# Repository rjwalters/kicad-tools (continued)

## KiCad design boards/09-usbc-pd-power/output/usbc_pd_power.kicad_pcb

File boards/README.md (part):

# kicad-tools Demo Boards

PCB designs and developing examples demonstrating kicad-tools capabilities. Each board includes a `.kct` project specification file describing the design intent, requirements, and progress.

## Quick Start

The easiest way to build any demo is using the `kct build` command:

```bash
# Build any project (runs full pipeline: schematic → PCB → route → verify)
kct build boards/01-voltage-divider

# Or specify a .kct file directly
kct build boards/02-charlieplex-led/project.kct

# Run individual steps
kct build boards/01-voltage-divider --step schematic
kct build boards/01-voltage-divider --step pcb
kct build boards/01-voltage-divider --step route
kct build boards/01-voltage-divider --step verify

# Preview what would happen without running
kct build boards/01-voltage-divider --dry-run

# Target a specific manufacturer for DRC verification
kct build boards/01-voltage-divider --mfr jlcpcb
```

## Board Status

| # | Board | Status | Components | Nets | Notes |
|---|-------|--------|------------|------|-------|
| 00 | [Simple LED](00-simple-led/) | Assembly ready | 3 | 3 | THT parts fab-assembled (procurement review). |
| 01 | [Voltage Divider](01-voltage-divider/) | Assembly ready | 4 | 3 | THT parts fab-assembled (procurement review). |
| 02 | [Charlieplex LED](02-charlieplex-led/) | Assembly ready · 1 known issue | 19 | 12 | Real ATtiny85, compiled firmware; THT MCU and headers fab-assembled (procurement review). Advisory [#7220] (vias at R3/R4 pad edges). |
| 03 | [USB Joystick](03-usb-joystick/) | **Not ready** (known defect) | 38 | 27 | Real ATmega32U4 HID circuit; four-layer filled/capped via process. Defect [#7250]: USB pair 71.6 Ω vs the 90 Ω spec. Advisory [#7220]. |
| 04 | [STM32 Dev Board](04-stm32-devboard/) | Assembly ready · 1 known issue | 17 | 12 | Correct MCP1825S regulator; paid 0.15 mm mechanical drills (exception [#6269], ruling #7147). |
| 05 | [BLDC Motor Controller](05-bldc-motor-controller/) | Assembly ready · 2 known issues | 42 | 37 | DRV8313 + ATmega328P; firmware and conservative bring-up limits supplied. Order 1 oz inner copper (advisory [#7209]). Advisory [#7220]. |
| 06 | [Four-channel LVDS demo](06-diffpair-test/) | Assembly ready | 36 | 18 | Real SN65LVDS1/2, four-layer stack with outer-layer signals; three manual headers. |
| 07 | [8 MiB SDRAM exerciser](07-matchgroup-test/) | Assembly ready | 43 | 55 | STM32F429 + IS42S16400J, six layers, 48 MHz SDRAM; legacy Epic [#2661] fixture archived. |
| 08 | [Precision acquisition](08-precision-acquisition/) | Planned | — | — | Four simultaneous differential ADC channels with USB streaming. |
| 09 | [USB-C PD power supply](09-usbc-pd-power/) | Development | 47 | 32 | Real PD sink, 5 V / 3 A target buck and Kelvin telemetry; routing/procurement pending. |

Assembly readiness applies only to the exact checked source and manufacturing
package bound by each `output/readiness.json`. Each report also records its
board's open `known_issues` (Issue #7261): an open **defect** keeps the board
not ready; **exceptions** and **advisories** are disclosed but keep it ready.
`kct fleet status` shows them (`YES*` / `known: #N`). Hardware testing remains pending.
Follow each board's fabrication process and manual-assembly instructions;
regenerating a board requires fresh validation and export. See the
[readiness audit](../docs/demo-readiness-2026-09-09.md) for evidence and tool issues.

## Prerequisites for Manual Build

Before running board generation scripts directly, set up the development environment:

```bash
# From repository root
uv sync --extra dev
```

This installs kicad-tools and all dependencies. See the [main README](../README.md#development) for details.

## Advanced: Manual Build

For more control, you can run individual Python scripts directly:

```bash
# Run any board's generation script (from repo root)
uv run python boards/01-voltage-divider/generate_design.py

# Or activate the virtual environment first
source .venv/bin/activate  # Linux/macOS
python boards/01-voltage-divider/generate_design.py
```

### Post-Build Commands

After building, you can run additional verification and export commands:

```bash
# Check for DRC violations with manufacturer rules
kct check output/voltage_divider_routed.kicad_pcb --mfr jlcpcb

# Generate BOM
kct bom output/voltage_divider.kicad_sch --format csv

# Export Gerbers (via KiCad or kicad-cli)
# Open the .kicad_pcb file in KiCad and use File > Plot
```

See individual board READMEs for board-specific details.

## Routing Entry Point Conventions

When writing a new board's `generate_design.py`, pick the routing entry point
that matches the design's signal characteristics.  The recommended pattern,
derived from the architectural review in [#3072], is:

| Design has... | Recommended entry | Boards using this pattern |
|---|---|---|
| No differential pairs and no length-matching | `subprocess.run(["kct", "route", ...])` *or* in-process `router.route_all()` | 00, 01, 02, 04 |
| Differential pairs (USB2/USB3/PCIe/MIPI/HDMI/etc.) | `subprocess.run(["kct", "route", ..., "--differential-pairs"])` *or* in-process `router.route_all_with_diffpairs(diffpair_config=...)` | 03, 05, 06 |
| Match-groups (SDR SDRAM) | See `boards/07-matchgroup-test/real_design/` for the reviewed six-layer source and independent timing/load checks | 07 |

### Why this matters

`router.route_all()` (and `kct route` without `--differential-pairs`) run a
per-net A* loop that is unaware of `DifferentialPair` metadata.  On a board
with diff pairs, this path silently bypasses Phase A (`CoupledPathfinder`)
and Phase B (intra-pair clearance rip-up), producing routes that violate
the `intra_pair_clearance`, `coupled_continuity_threshold`, and
`target_diff_impedance` constraints declared in the project.

`router.route_all_with_diffpairs()` (and `kct route --differential-pairs`)
invoke the Phase A/B pipeline explicitly.  PR #3069 (board 03) and PR #3090
(board 06) migrated to this entry after the bypass bug was diagnosed.

> **✅ Recipe restored ([#3922]):** the #3308/#3410 recipe consolidation had
> silently dropped `--differential-pairs` from board 03's routing recipe
> (`generate_design.py:route_pcb()`), so the recipe no longer even *requested*
> diff-pair routing and this README's claim went false. The flag (plus
> `--net-class-map`, which forwards the D+/D- `intra_pair_clearance` metadata
> and engages the validate-side diff-pair DRC rules) is now restored and
> mirrored in `tests/router/test_board03_routing_baseline.py`, guarded by
> `test_recipe_includes_differential_pairs_flag()` so a future consolidation
> cannot drop it silently again.
>
> **Known limitation — runtime coupling gated on [#3952]:** on board 03 the
> flag is currently **inert at routing time**. The board's fine-pitch USB-C
> (J1) and QFP-32 (U1) force the CLI's escape-routing dispatch, and
> `route_cmd`'s escape / auto-layers-escalation paths do not consult
> `args.differential_pairs` — so the `CoupledPathfinder` pre-pass
> (`route_all_with_diffpairs`) never runs and the D+/D- skew remains
> coincidental rather than constructed. The recipe deliberately keeps
> `--auto-layers` (the default) because it preserves the escape pre-phase
> board 03 needs for **13/13 + 0 native DRC**; forcing the diff-pair path with
> `--no-auto-layers` *does* invoke Phase A but drops escape routing and
> reintroduces a `kicad-cli` clearance violation. Integrating diff-pair
> routing into the escape path (so Phase A runs *with* escape routing at 0
> DRC) is tracked in [#3952] (adjacent to the `CoupledPathfinder` convergence
> work in [#3921]). The behavior is pinned by an xfail'd
> `test_coupled_pathfinder_phase_a_invoked` that will flip to XPASS when
> [#3952] lands.

### Determinism and artifact churn (`--seed`)

Routing is deterministic **per router version**: two runs that share a
`--seed` at the same code version emit a byte-identical routed
`.kicad_pcb`. This is what lets a same-seed regen produce a zero-line
`git diff` and what the board-06 determinism harness
(`scripts/ci/board06_determinism_smoke.sh`,
`tests/router/test_board06_determinism.py`) relies on. The property is
implemented by `enable_deterministic_uuids()` in
`router/primitives.py`, which derives every segment/via UUID from the
seeded global RNG instead of `uuid.uuid4()`.

Two caveats:

- **Determinism is per-router-version, not forever.** A regen produced by
  a *newer* router may legitimately differ from a committed artifact
  (geometry improvements, quantization changes, new escape logic). An
  artifact-vs-regen diff across router versions is expected; only
  fresh-vs-fresh at the *same* version is guaranteed byte-identical.
- **Segment/via serialization matches KiCad's canonical field order**
  (`... uuid net`, uuid before net; issue #3925). Emitting `net` before
  `uuid` used to churn every segment and via on the first KiCad open/save
  round-trip, drowning real changes in reformat noise. If you regenerate a
  board and see a large diff with no geometric change, confirm you are
  comparing same-version fresh-vs-fresh before assuming a router bug.
- **Board 06 is a known exception downstream of its coupled diff-pair
  pre-phase**: full-regen output is run-to-run nondeterministic even at a
  fixed version and seed (issue #4536, open). The pre-phase itself
  (shadow construction) *is* deterministic and is the correct surface to
  measure a change against --- see [`boards/06-diffpair-test/README.md`
  "Measuring Changes"](06-diffpair-test/README.md#measuring-changes-the-shadow-phase-is-deterministic-full-regen-is-not-4536)
  for the two stable downstream modes and the paired-comparison
  convention. Do not assume the smoke test above proves full-board
  byte-identity on this one board.

### Subprocess (`kct route`) vs. in-process (`router.route_all_*`)

Both are supported.  The subprocess path (`subprocess.run(["kct", "route", ...])`)
is preferred for new boards because:

- It is the production routing path; in-process tests can drift from it.
- CLI flags (`--strategy`, `--iterations`, `--differential-pairs`,
  `--net-class-map`, `--seed`) are validated end-to-end by CI.
- Zone-fill, post-route DRC, and routed-PCB artifact emission are handled
  automatically (see `route_cmd._fill_zones_after_route`).

The in-process path remains the right choice when a board needs to:

- Inject custom logic between routing and post-processing (e.g. board 06's
  custom diff-pair config plumbing).
- Exercise router internals that the CLI does not yet expose (e.g.
  `DifferentialPairConfig.per_pair_max_iterations`,
  `enable_shadow_construction`, or board 06's tightly-coupled width
  re-solve). Note: per-class values like `intra_pair_clearance` **do**
  survive the CLI's JSON sidecar round-trip (`kct route --net-class-map`,
  #2996) — an earlier version of this section claimed otherwise; that claim
  was verified false in the 2026-07-05 sweep.

### Architectural decision: auto-detect was rejected

[#3072] explicitly considered teaching `router.route_all()` (and the CLI's
default path) to auto-detect diff pairs and short-circuit to the
Phase-A/B-aware entry.  The decision was to **not** auto-detect, for two
reasons:

1. The remaining footgun is procedural (new boards forget the right entry).
   **Update 2026-07-05: the footgun bit** --- board 03 lost its
   diff-pair-aware entry in a later recipe consolidation without anyone
   noticing ([#3922]), exactly the failure mode auto-detect would have
   prevented. The flag was restored and a recipe-contract test now guards
   it ([#3922]); note the restored flag is still inert on board 03 until the
   route_cmd escape/diff-pair dispatch is fixed ([#3952]). The procedural
   footgun remains for the *next* new board — weigh this when re-promoting
   the auto-detect work.
2. An auto-detect change would have to land on both surfaces (in-process
   and CLI) to be complete, and the `CoupledPathfinder` latency issue
   tracked in [#3089] makes a CLI-default flip premature.

Re-promote the auto-detect work as a separate issue once [#3089] resolves
and a regression baseline exists for board 06's escape-time behavior.

[#3072]: https://github.com/rjwalters/kicad-tools/issues/3072
[#3089]: https://github.com/rjwalters/kicad-tools/issues/3089

## Known Issues

These are known limitations that may affect your experience:

| Issue | Affects | Description |
|-------|---------|-------------|
| [#659] | 02, 03 | Trace optimization may be needed for dense designs (02 now routes 8/8 as of 2026-07-05) |
| [#661] | All | Router doesn't always warn about DRC violations |
| [#3918] | All | `kct build` currently cannot complete on any demo board — use each board's `generate_design.py`/`design.py` recipe until the orchestrator fixes land |

[#659]: https://github.com/rjwalters/kicad-tools/issues/659
[#661]: https://github.com/rjwalters/kicad-tools/issues/661
[#3918]: https://github.com/rjwalters/kicad-tools/issues/3918
[#3921]: https://github.com/rjwalters/kicad-tools/issues/3921
[#3922]: https://github.com/rjwalters/kicad-tools/issues/3922
[#3766]: https://github.com/rjwalters/kicad-tools/issues/3766
[#3952]: https://github.com/rjwalters/kicad-tools/issues/3952

## Pad pin types (`pintype`)

KiCad's "Update PCB from Schematic" writes each schematic pin's name and
electrical type onto its pad (`(pinfunction "VDD") (pintype "power_in")`).
`kct detect-mistakes` treats `power_in`/`power_out` pads as power-rail
evidence, which catches rails the name heuristic misses (`VREG_1V2`, `VCAP1`).
The generators write PCBs directly, so they have to add this data
themselves ([#5985]):

- **Board 09** calls `annotate_pcb_file_pintypes(pcb_path, sch_path)` right
  after it writes the PCB, and its committed output carries `pintype` ([#5998]). A buck converter's switch-node pin
  (`SW`, `LX`, `PH`) is typed `power_out`, but `kct detect-mistakes` does not
  treat the switch node as a rail.
- **Boards 00 and 01** call it right after they write the unrouted PCB, and
  their committed unrouted and routed outputs carry `pintype` ([#6025]).
  Every pin on these boards is `passive`, so no new rails appear.
- **Board 02** calls it right after it writes the unrouted PCB. Its
  committed unrouted and routed outputs carry `pintype`, annotated in place
  so the committed copper is unchanged, and `package_release.py` rewrote its
  readiness package ([#6025]).
- **Board 03** calls it from `generate_design.py` right after it writes the
  unrouted PCB (`write_pcb`). The reviewed routing plan is replayed onto that
  PCB, so the routed PCB inherits the annotation. Its committed unrouted and
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
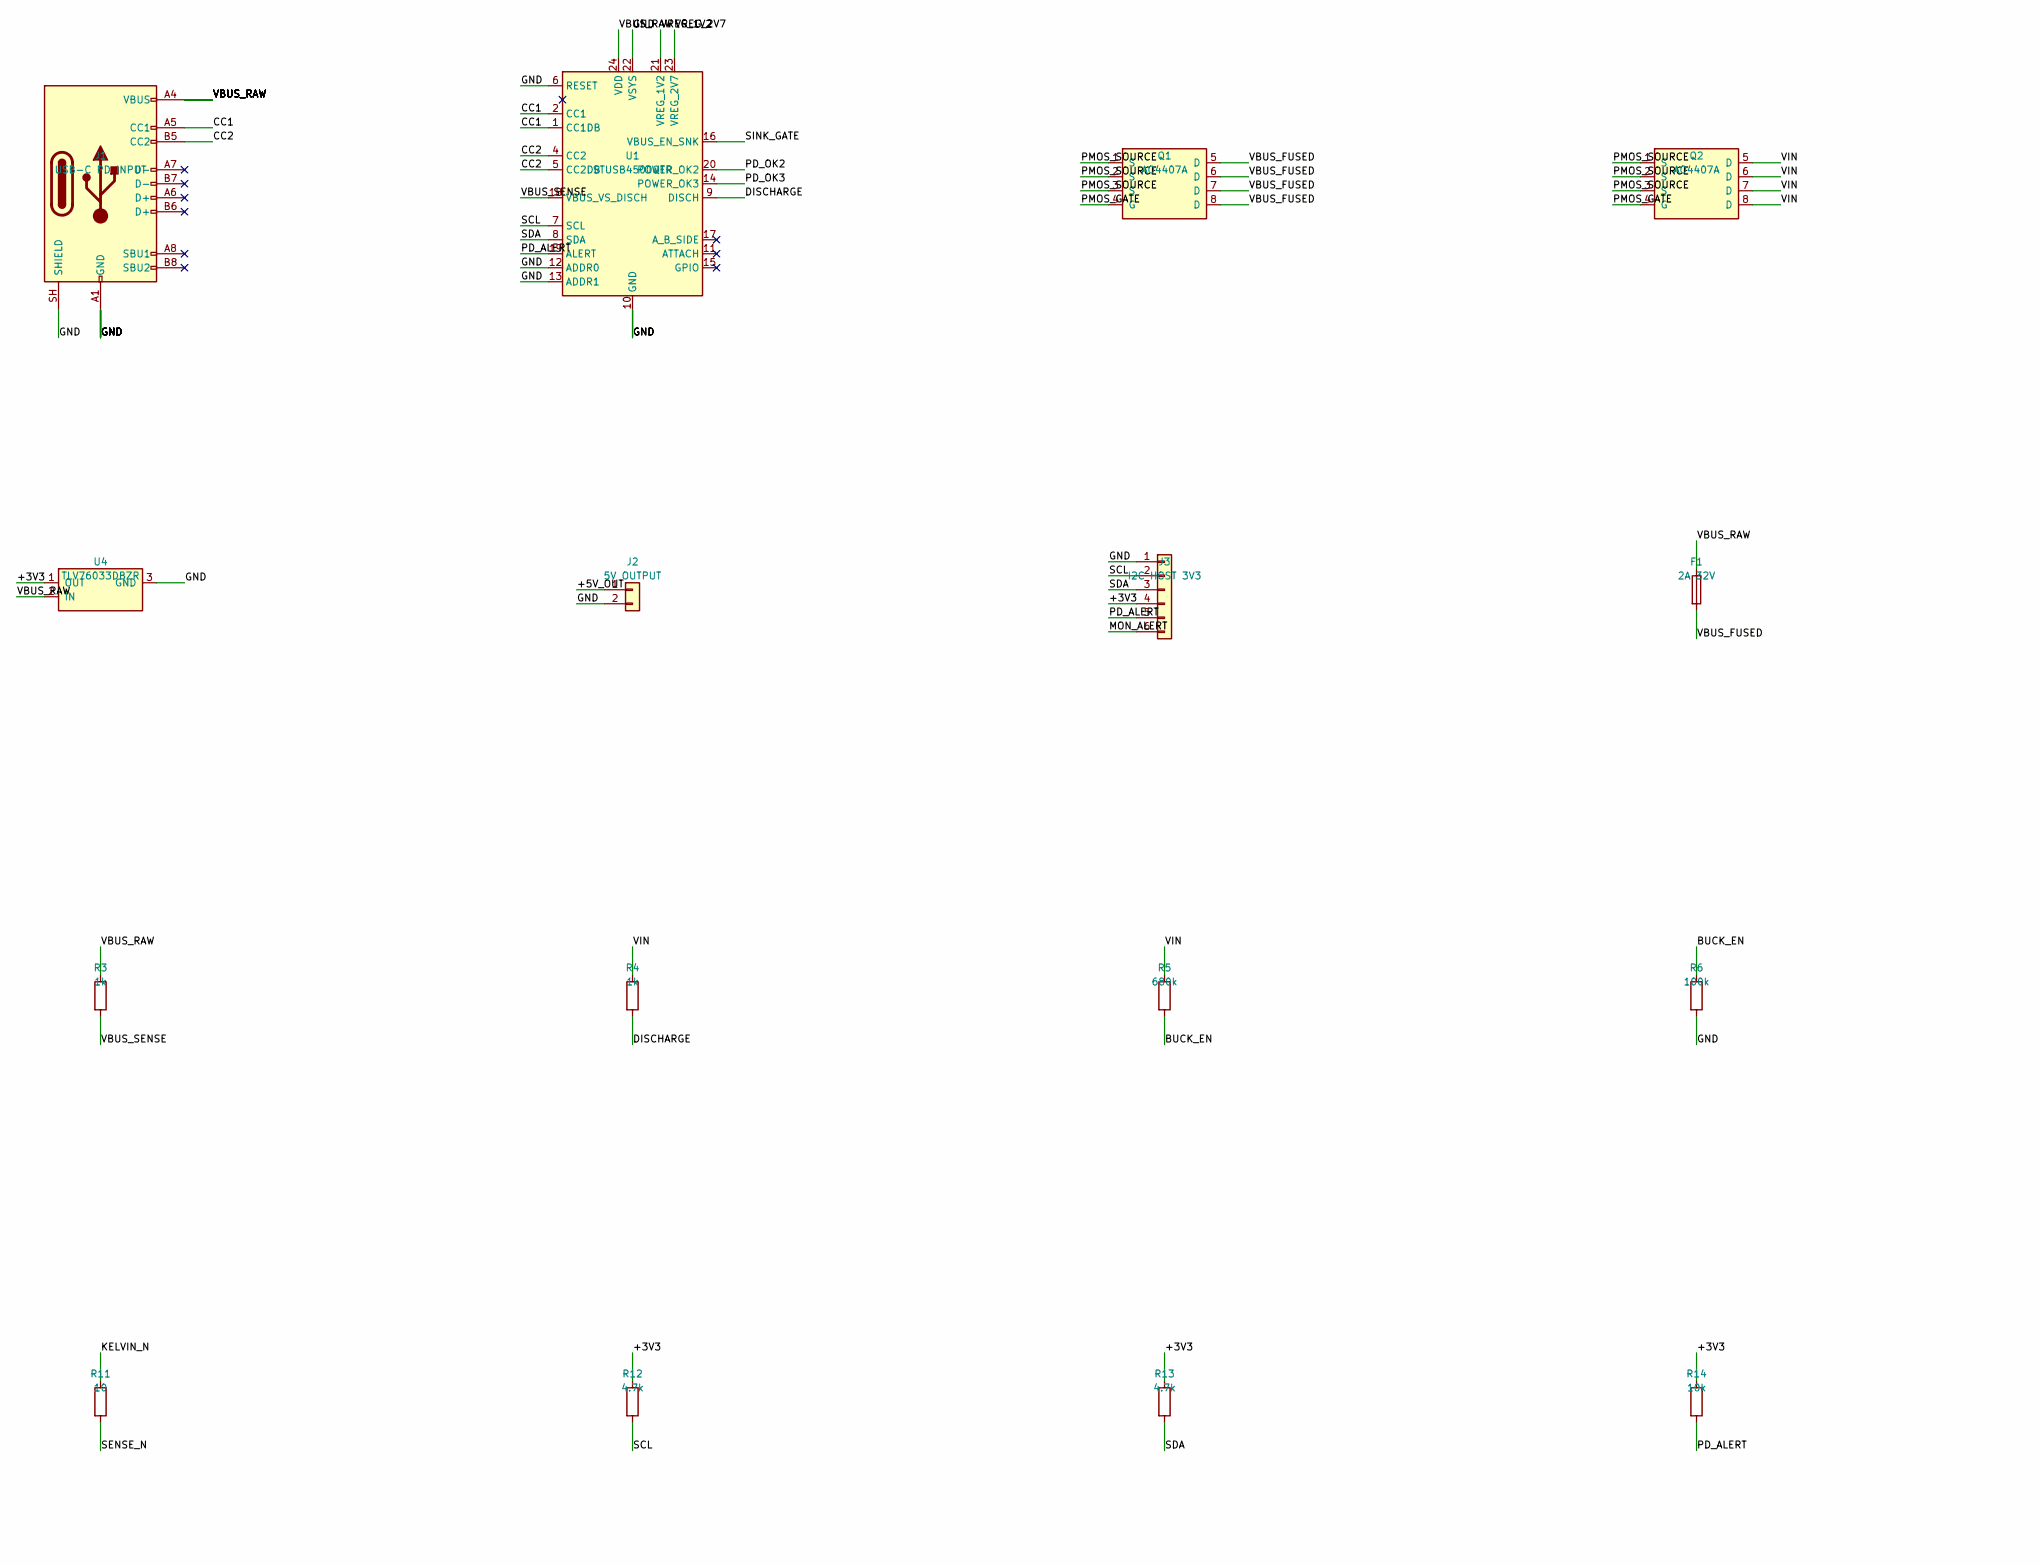
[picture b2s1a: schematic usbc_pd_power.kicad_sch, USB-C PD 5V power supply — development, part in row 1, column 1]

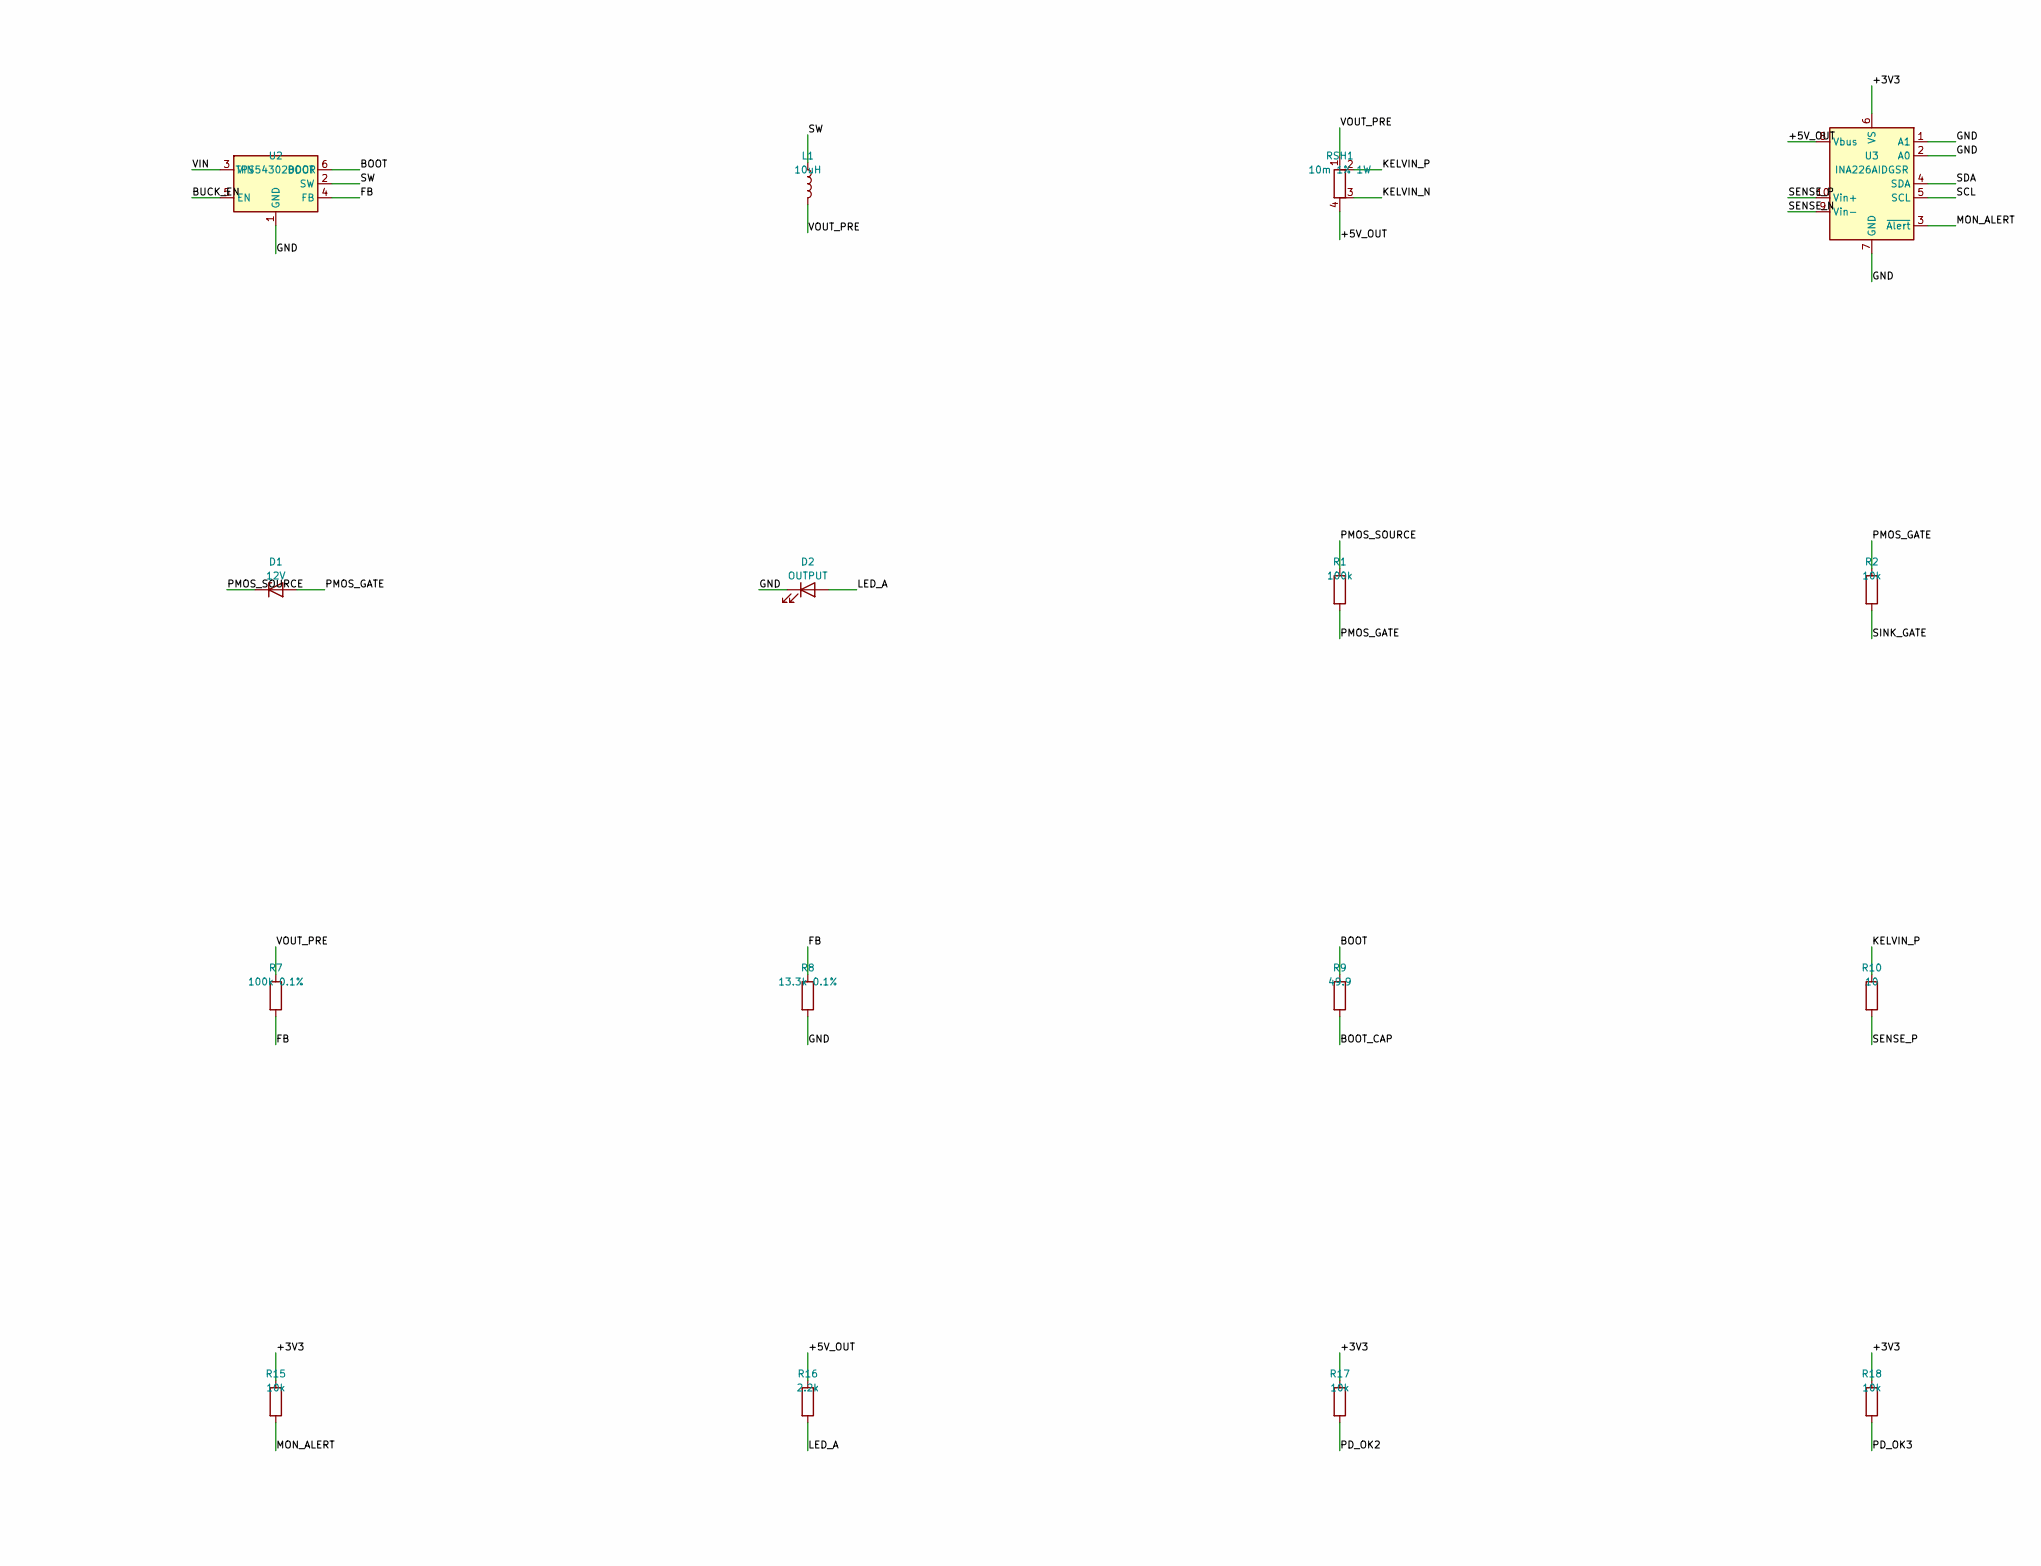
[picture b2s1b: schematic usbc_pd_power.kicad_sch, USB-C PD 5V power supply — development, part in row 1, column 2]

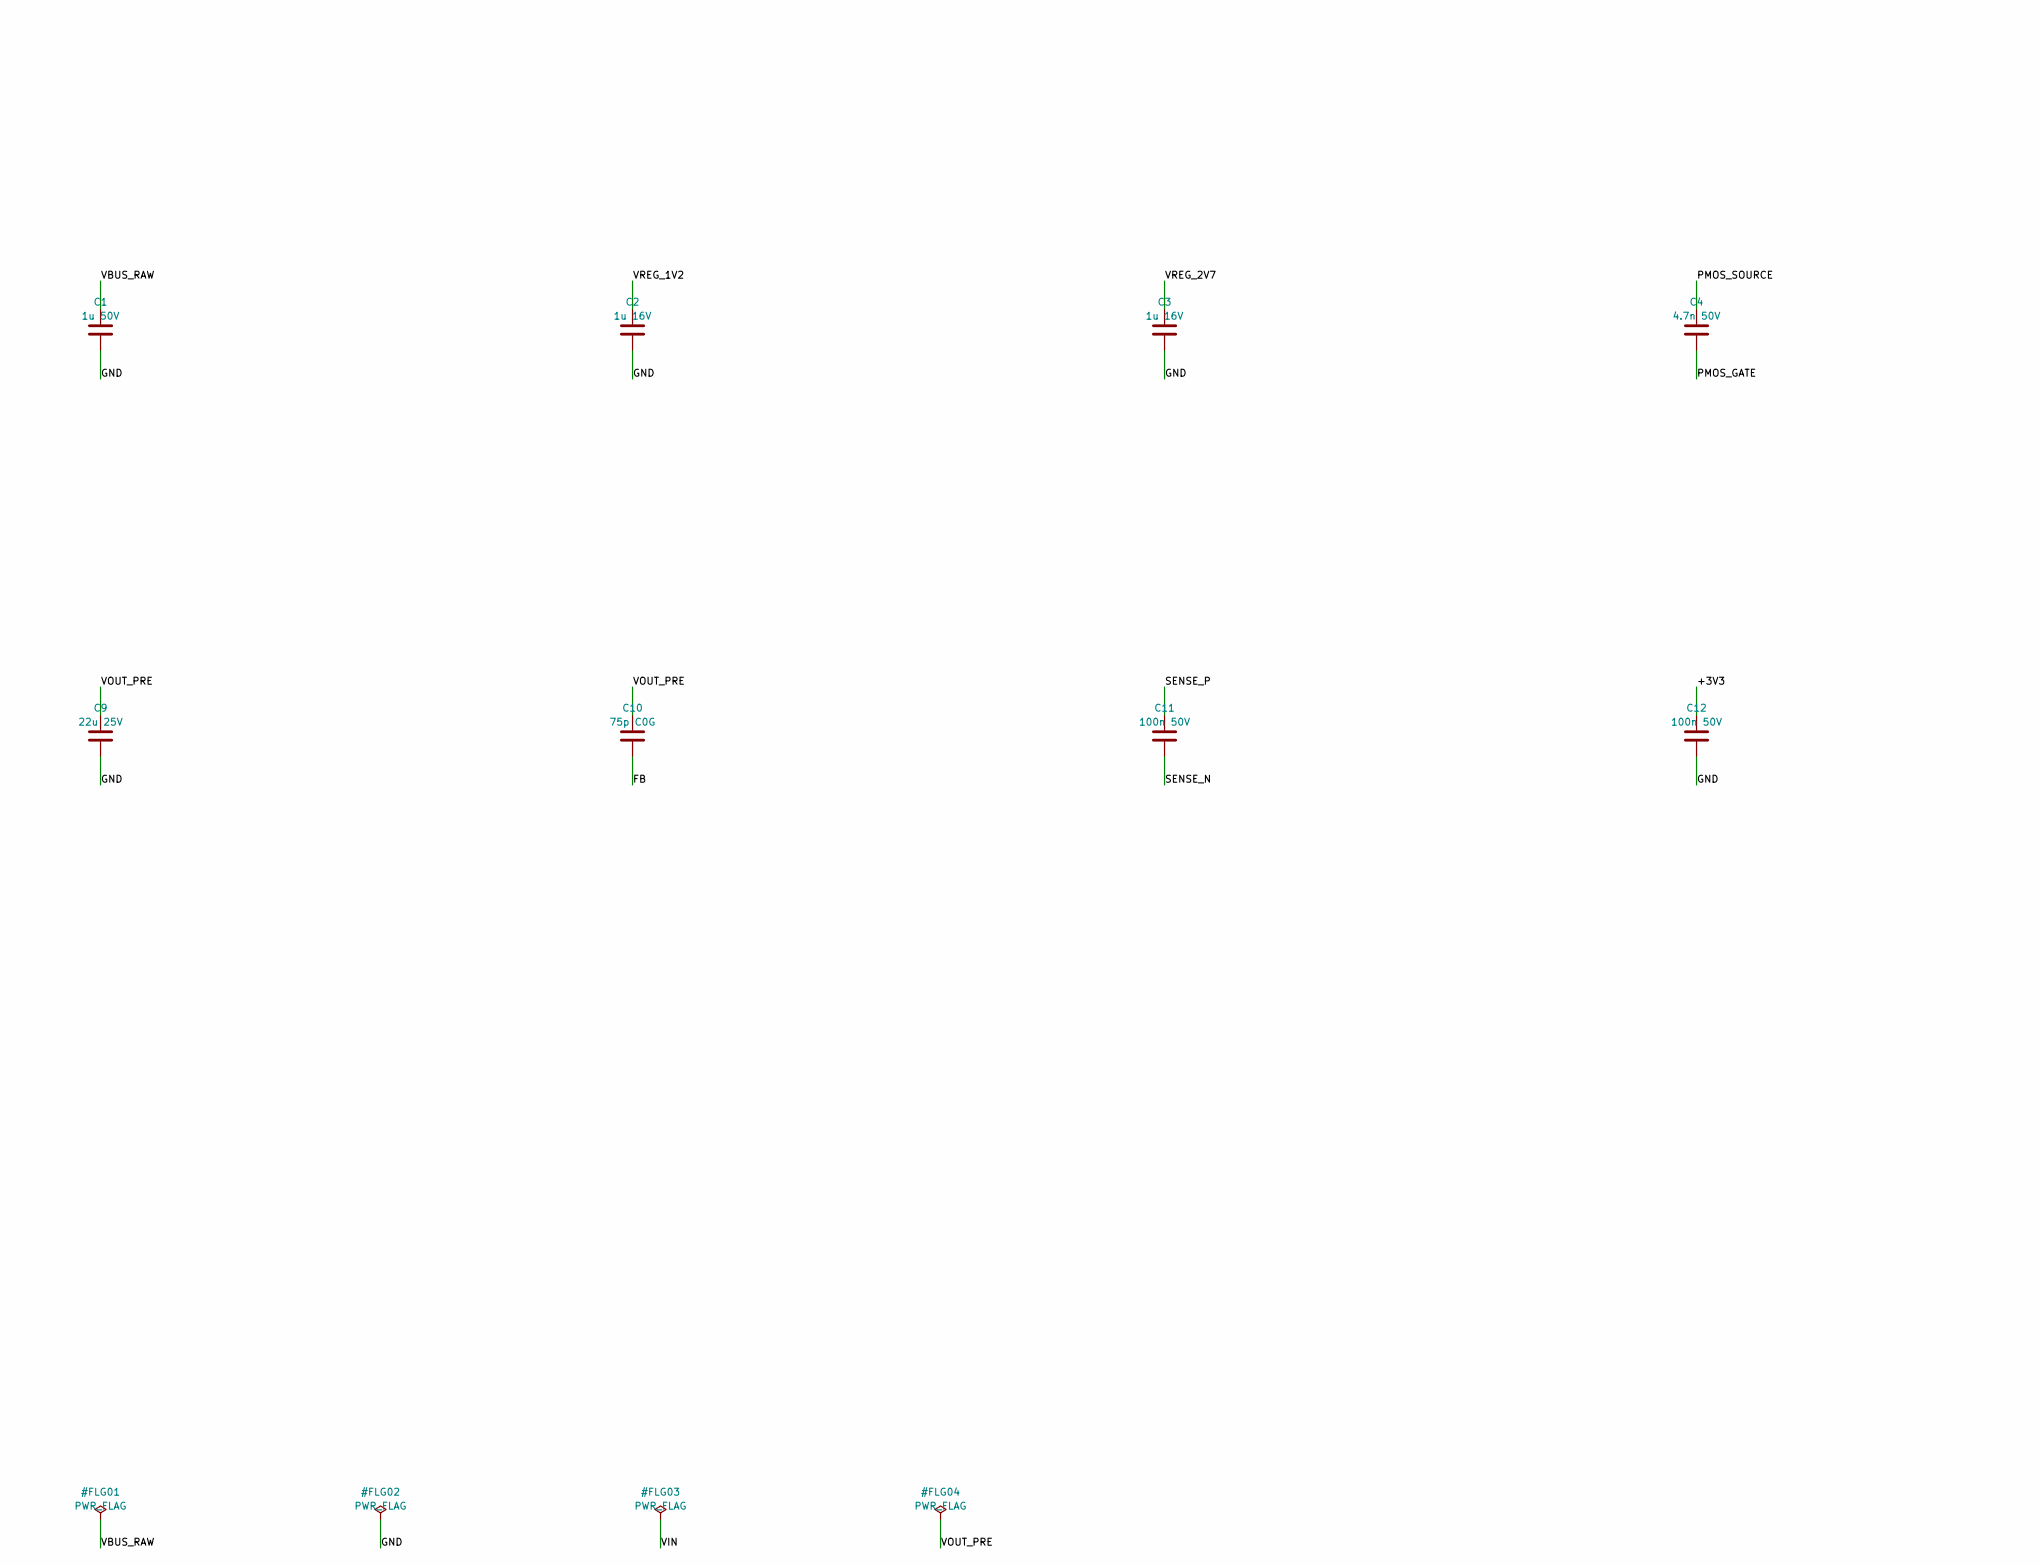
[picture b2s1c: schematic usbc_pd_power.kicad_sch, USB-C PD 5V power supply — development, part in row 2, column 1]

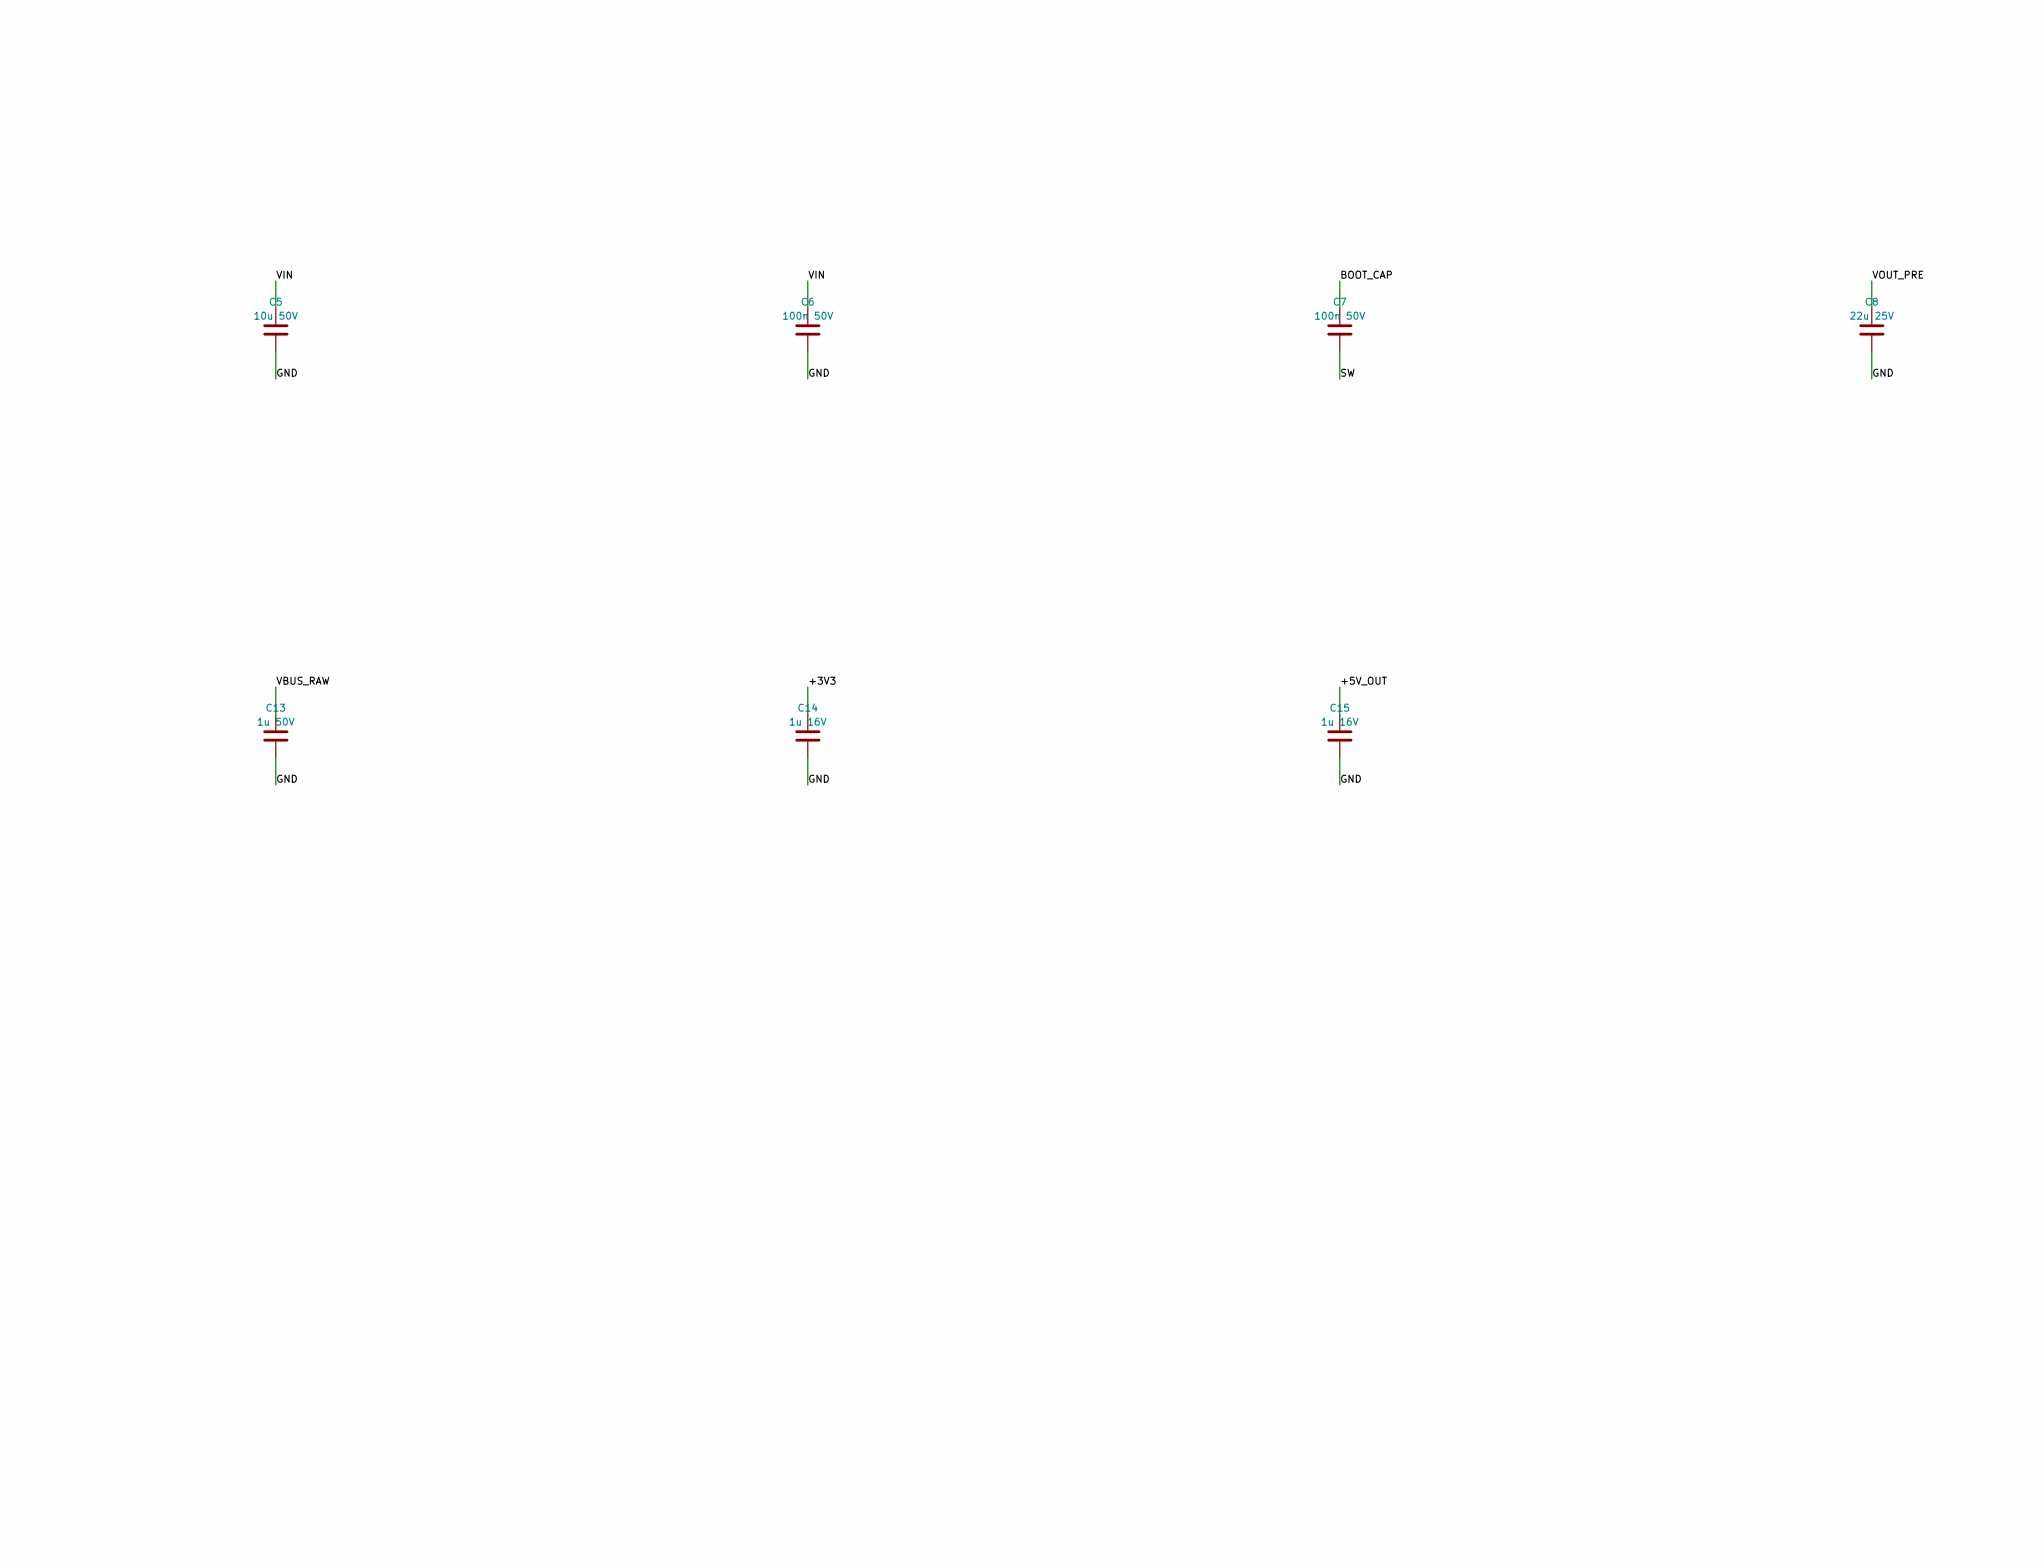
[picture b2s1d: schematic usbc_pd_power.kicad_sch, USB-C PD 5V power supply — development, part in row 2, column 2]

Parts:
C1, C13: 1u 50V; C_0603_1608Metric
C2, C3, C14, C15: 1u 16V; C_0603_1608Metric
C4: 4.7n 50V; C_0603_1608Metric
C5: 10u 50V; C_1206_3216Metric; Manufacturer_Part_Number CL31B106KBHNNNE; LCSC C89632
C6, C7, C11, C12: 100n 50V; C_0603_1608Metric; Manufacturer_Part_Number CC0603KRX7R9BB104; LCSC C14663
C8, C9: 22u 25V; C_1206_3216Metric; Manufacturer_Part_Number CL31A226KAHNNNE; LCSC C12891
C10: 75p C0G; C_0603_1608Metric
D1: 12V; D_SOD-123; Manufacturer_Part_Number BZT52C12
D2: OUTPUT; LED_0603_1608Metric; Manufacturer_Part_Number LTST-C190KGKT; LCSC C125094
F1: 2A 32V; Fuse_1206_3216Metric; Manufacturer_Part_Number 0467002.NR
J1: USB-C PD INPUT; USB_C_Receptacle_HRO_TYPE-C-31-M-12; Manufacturer_Part_Number TYPE-C-31-M-12; LCSC C165948
J2: 5V OUTPUT; TerminalBlock_Phoenix_MKDS-1,5-2-5.08_1x02_P5.08mm_Horizont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; Manufacturer_Part_Number MKDS 1,5/2-5,08
J3: I2C HOST 3V3; PinHeader_1x06_P2.54mm_Vertical; Manufacturer_Part_Number TSW-106-07-G-S
L1: 10uH; SRP7050TA; Manufacturer_Part_Number SRP7050TA-100M; LCSC C2041441
Q1, Q2: AO4407A; SOIC-8_3.9x4.9mm_P1.27mm; Manufacturer_Part_Number AO4407A; LCSC C16072
R1, R6: 100k; R_0603_1608Metric
R2, R14, R15, R17, R18: 10k; R_0603_1608Metric
R3, R4: 1k; R_1206_3216Metric; Manufacturer_Part_Number CRCW12061K00FKEAHP; LCSC C844867
R5: 680k; R_0603_1608Metric
R7: 100k 0.1%; R_0603_1608Metric; Manufacturer_Part_Number RT0603BRD07100KL; LCSC C122538
R8: 13.3k 0.1%; R_0603_1608Metric; Manufacturer_Part_Number RT0603BRD0713K3L; LCSC C861117
R9: 49.9; R_0603_1608Metric
R10, R11: 10; R_0603_1608Metric
R12, R13: 4.7k; R_0603_1608Metric
R16: 2.2k; R_0603_1608Metric
RSH1: 10m 1% 1W; R_Shunt_Vishay_WSK2512_6332Metric_T1.19mm; Manufacturer_Part_Number WSK2512R0100FEA; LCSC C3985410
U1: STUSB4500QTR; QFN-24-1EP_4x4mm_P0.5mm_EP2.6x2.6mm; Manufacturer_Part_Number STUSB4500QTR; LCSC C2678061
U2: TPS54302DDCR; TSOT-23-6; Manufacturer_Part_Number TPS54302DDCR; LCSC C311983
U3: INA226AIDGSR; MSOP-10_3x3mm_P0.5mm; Manufacturer_Part_Number INA226AIDGSR; LCSC C49851
U4: TLV76033DBZR; SOT-23; Manufacturer_Part_Number TLV76033DBZR; LCSC C2683368

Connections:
+3V3: C12.1, C14.1, J3.4, R12.1, R13.1, R14.1, R15.1, R17.1, R18.1, U3.6 (VS), U4.1 (OUT)
+5V_OUT: C15.1, J2.1, R16.1, RSH1.4, U3.8 (Vbus)
BOOT: R9.1, U2.6 (BOOT)
BOOT_CAP: C7.1, R9.2
BUCK_EN: R5.2, R6.1, U2.5 (EN)
CC1: J1.A5 (CC1), U1.1 (CC1DB), U1.2 (CC1)
CC2: J1.B5 (CC2), U1.4 (CC2), U1.5 (CC2DB)
DISCHARGE: R4.2, U1.9 (DISCH)
FB: C10.2, R7.2, R8.1, U2.4 (FB)
GND: C1.2, C2.2, C3.2, C5.2, C6.2, C8.2, C9.2, C12.2, C13.2, C14.2, C15.2, D2.1 (K), J1.A1 (GND), J1.A12 (GND), J1.B1 (GND), J1.B12 (GND), J1.SH (SHIELD), J2.2, J3.1, R6.2, R8.2, U1.6 (RESET), U1.10 (GND), U1.12 (ADDR0), U1.13 (ADDR1), U1.22 (VSYS), U1.25 (GND), U2.1 (GND), U3.1 (A1), U3.2 (A0), U3.7 (GND), U4.3 (GND)
KELVIN_N: R11.1, RSH1.3
KELVIN_P: R10.1, RSH1.2
LED_A: D2.2 (A), R16.2
MON_ALERT: J3.6, R15.2, U3.3 (~Alert)
PD_ALERT: J3.5, R14.2, U1.19 (ALERT)
PD_OK2: R17.2, U1.20 (POWER_OK2)
PD_OK3: R18.2, U1.14 (POWER_OK3)
PMOS_GATE: C4.2, D1.2 (A), Q1.4 (G), Q2.4 (G), R1.2, R2.1
PMOS_SOURCE: C4.1, D1.1 (K), Q1.1 (S), Q1.2 (S), Q1.3 (S), Q2.1 (S), Q2.2 (S), Q2.3 (S), R1.1
SCL: J3.2, R12.2, U1.7 (SCL), U3.5 (SCL)
SDA: J3.3, R13.2, U1.8 (SDA), U3.4 (SDA)
SENSE_N: C11.2, R11.2, U3.9 (Vin-)
SENSE_P: C11.1, R10.2, U3.10 (Vin+)
SINK_GATE: R2.2, U1.16 (VBUS_EN_SNK)
SW: C7.2, L1.1, U2.2 (SW)
VBUS_FUSED: F1.2, Q1.5 (D), Q1.6 (D), Q1.7 (D), Q1.8 (D)
VBUS_RAW: C1.1, C13.1, F1.1, J1.A4 (VBUS), J1.A9 (VBUS), J1.B4 (VBUS), J1.B9 (VBUS), R3.1, U1.24 (VDD), U4.2 (IN)
VBUS_SENSE: R3.2, U1.18 (VBUS_VS_DISCH)
VIN: C5.1, C6.1, Q2.5 (D), Q2.6 (D), Q2.7 (D), Q2.8 (D), R4.1, R5.1, U2.3 (VIN)
VOUT_PRE: C8.1, C9.1, C10.1, L1.2, R7.1, RSH1.1
VREG_1V2: C2.1, U1.21 (VREG_1V2)
VREG_2V7: C3.1, U1.23 (VREG_2V7)

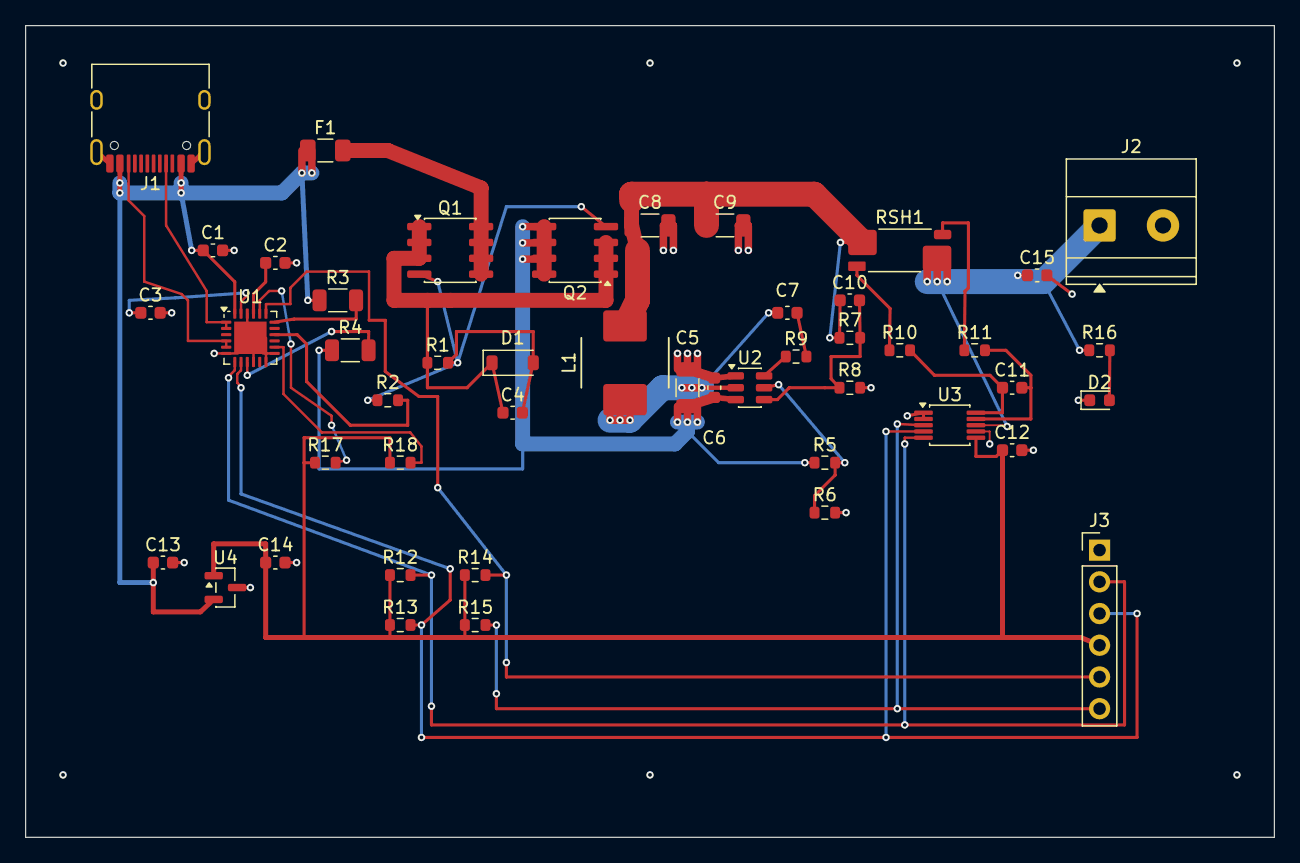
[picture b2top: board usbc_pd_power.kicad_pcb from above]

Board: 4 copper layers, 100.0 x 65.0 mm, 47 parts (0 on the bottom side), 32 nets.

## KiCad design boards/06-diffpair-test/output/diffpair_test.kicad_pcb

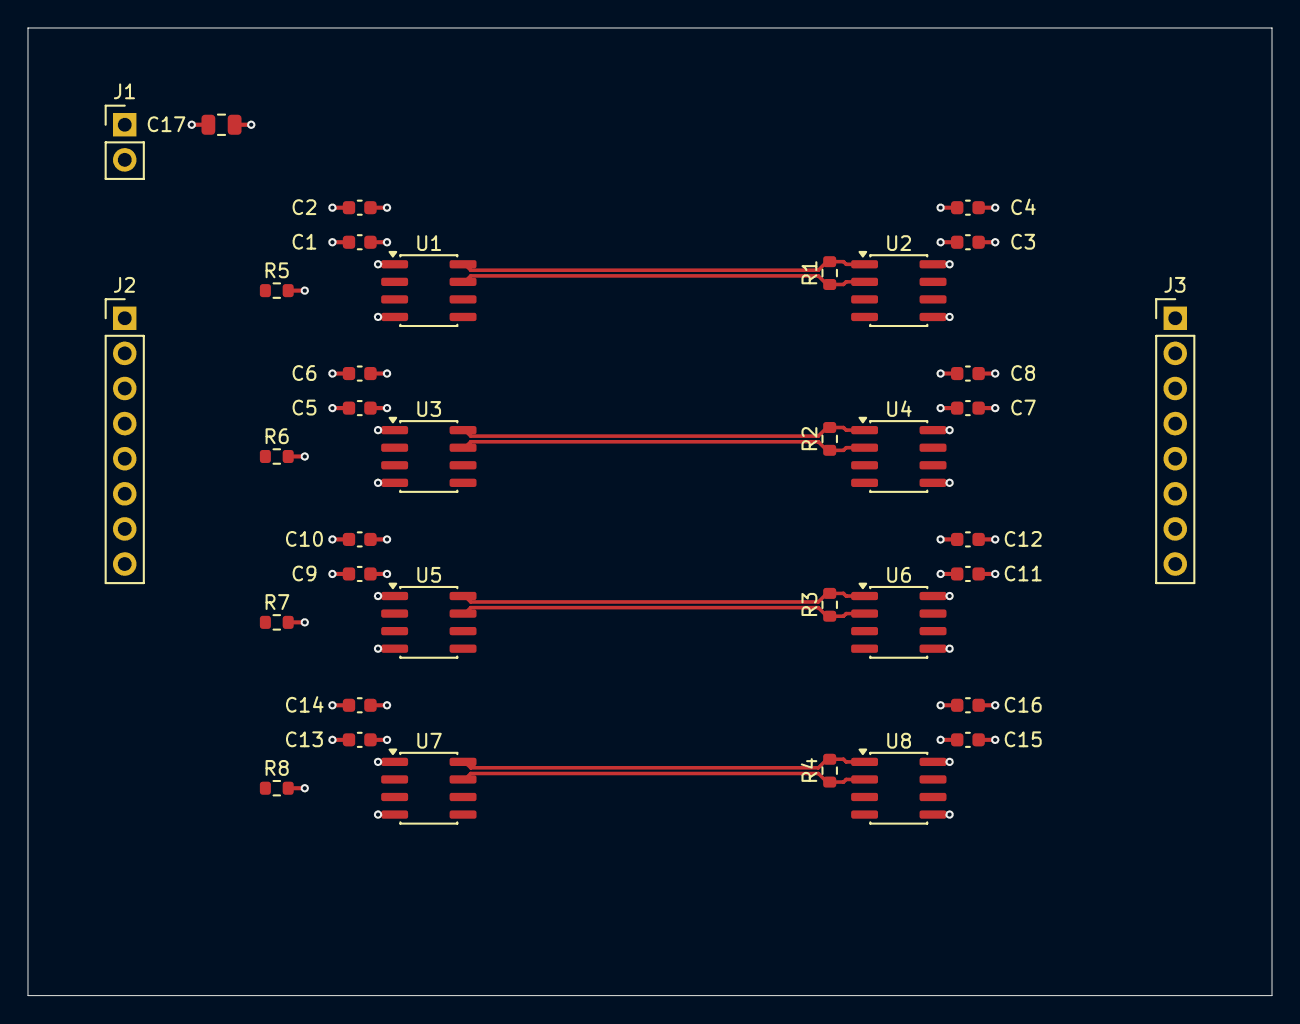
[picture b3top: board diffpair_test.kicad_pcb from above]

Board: 4 copper layers, 90.0 x 70.0 mm, 36 parts (0 on the bottom side), 18 nets.

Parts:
C1, C3, C5, C7, C9, C11, C13, C15: 1nF; C_0603_1608Metric
C2, C4, C6, C8, C10, C12, C14, C16: 100nF; C_0603_1608Metric
C17: 10uF; C_0805_2012Metric
J1: 3.3V regulated input; PinHeader_1x02_P2.54mm_Vertical
J2: IN1-4 / GND; PinHeader_1x08_P2.54mm_Vertical
J3: OUT1-4 / GND; PinHeader_1x08_P2.54mm_Vertical
R1, R2, R3, R4: 100; R_0603_1608Metric
R5, R6, R7, R8: 100k; R_0603_1608Metric
U1, U3, U5, U7: SN65LVDS1DR; SOIC-8_3.9x4.9mm_P1.27mm
U2, U4, U6, U8: SN65LVDS2DR; SOIC-8_3.9x4.9mm_P1.27mm

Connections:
+3V3: C1.1, C2.1, C3.1, C4.1, C5.1, C6.1, C7.1, C8.1, C9.1, C10.1, C11.1, C12.1, C13.1, C14.1, C15.1, C16.1, C17.1, J1.1, U1.1 (VCC), U2.8 (VCC), U3.1 (VCC), U4.8 (VCC), U5.1 (VCC), U6.8 (VCC), U7.1 (VCC), U8.8 (VCC)
GND: C1.2, C2.2, C3.2, C4.2, C5.2, C6.2, C7.2, C8.2, C9.2, C10.2, C11.2, C12.2, C13.2, C14.2, C15.2, C16.2, C17.2, J1.2, J2.2, J2.4, J2.6, J2.8, J3.2, J3.4, J3.6, J3.8, R5.2, R6.2, R7.2, R8.2, U1.4 (GND), U2.5 (GND), U3.4 (GND), U4.5 (GND), U5.4 (GND), U6.5 (GND), U7.4 (GND), U8.5 (GND)
IN1: J2.1, R5.1, U1.2 (D)
IN2: J2.3, R6.1, U3.2 (D)
IN3: J2.5, R7.1, U5.2 (D)
IN4: J2.7, R8.1, U7.2 (D)
LVDS1_N: R1.2, U1.8 (Z), U2.1 (B)
LVDS1_P: R1.1, U1.7 (Y), U2.2 (A)
LVDS2_N: R2.2, U3.8 (Z), U4.1 (B)
LVDS2_P: R2.1, U3.7 (Y), U4.2 (A)
LVDS3_N: R3.2, U5.8 (Z), U6.1 (B)
LVDS3_P: R3.1, U5.7 (Y), U6.2 (A)
LVDS4_N: R4.2, U7.8 (Z), U8.1 (B)
LVDS4_P: R4.1, U7.7 (Y), U8.2 (A)
OUT1: J3.1, U2.7 (R)
OUT2: J3.3, U4.7 (R)
OUT3: J3.5, U6.7 (R)
OUT4: J3.7, U8.7 (R)

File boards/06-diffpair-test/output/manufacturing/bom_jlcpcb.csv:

Comment,Designator,Footprint,LCSC Part #
100,"R1,R2,R3,R4",Resistor_SMD:R_0603_1608Metric,C22775
100k,"R5,R6,R7,R8",Resistor_SMD:R_0603_1608Metric,C25803
100nF,"C10,C12,C14,C16,C2,C4,C6,C8",Capacitor_SMD:C_0603_1608Metric,C14663
10uF,C17,Capacitor_SMD:C_0805_2012Metric,C15850
1nF,"C1,C11,C13,C15,C3,C5,C7,C9",Capacitor_SMD:C_0603_1608Metric,C1588
3.3V regulated input,J1,Connector_PinHeader_2.54mm:PinHeader_1x02_P2.54mm_Vertical,C492401
IN1-4 / GND,J2,Connector_PinHeader_2.54mm:PinHeader_1x08_P2.54mm_Vertical,C492407
OUT1-4 / GND,J3,Connector_PinHeader_2.54mm:PinHeader_1x08_P2.54mm_Vertical,C492407
SN65LVDS1DR,"U1,U3,U5,U7",Package_SO:SOIC-8_3.9x4.9mm_P1.27mm,C2671256
SN65LVDS2DR,"U2,U4,U6,U8",Package_SO:SOIC-8_3.9x4.9mm_P1.27mm,C2671054
